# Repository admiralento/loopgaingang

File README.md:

# loopgaingang

EE372B project: a custom LDO test board (JAFWAK), and the tools to characterize it.

| Folder | What's in it |
|---|---|
| `LDO_Stable_JAFWAK/` | KiCad project for our board. Sub-sheets: `ldo_harness`, `buffer` (BUF634 for line transient / PSRR), `load_cell` (on-board switched load), `rc_filter`, `temp_sense`. Gerbers in `Out/`, BOM in `bom/`, PDFs in `Schematic PDFs/` and `LayoutLayers/`. |
| `TPS7A7001_Evaluation_Board/` | KiCad project for the TPS7A7001 demo board (1.0 V out), used to bring up the bench before our board. |
| `Switched_R_Load_Bank/` | KiCad project for the separate 5-bit switched resistor load used with the demo board. |
| `AD_workspaces/` | WaveForms workspaces and the JavaScript settling-time script for manual measurements with the Analog Discovery. |
| `ldo_bench/` | Python bench automation: load / line regulation, load / line transient, PSRR, quiescent current and enable tests, driven from the command line. **Start with [`ldo_bench/README.md`](ldo_bench/README.md).** |

The automated tests and the WaveForms workspaces use the same settling analysis (`ldo_bench` ports `AD_workspaces/load_tran_script.js`), so they give the same numbers.

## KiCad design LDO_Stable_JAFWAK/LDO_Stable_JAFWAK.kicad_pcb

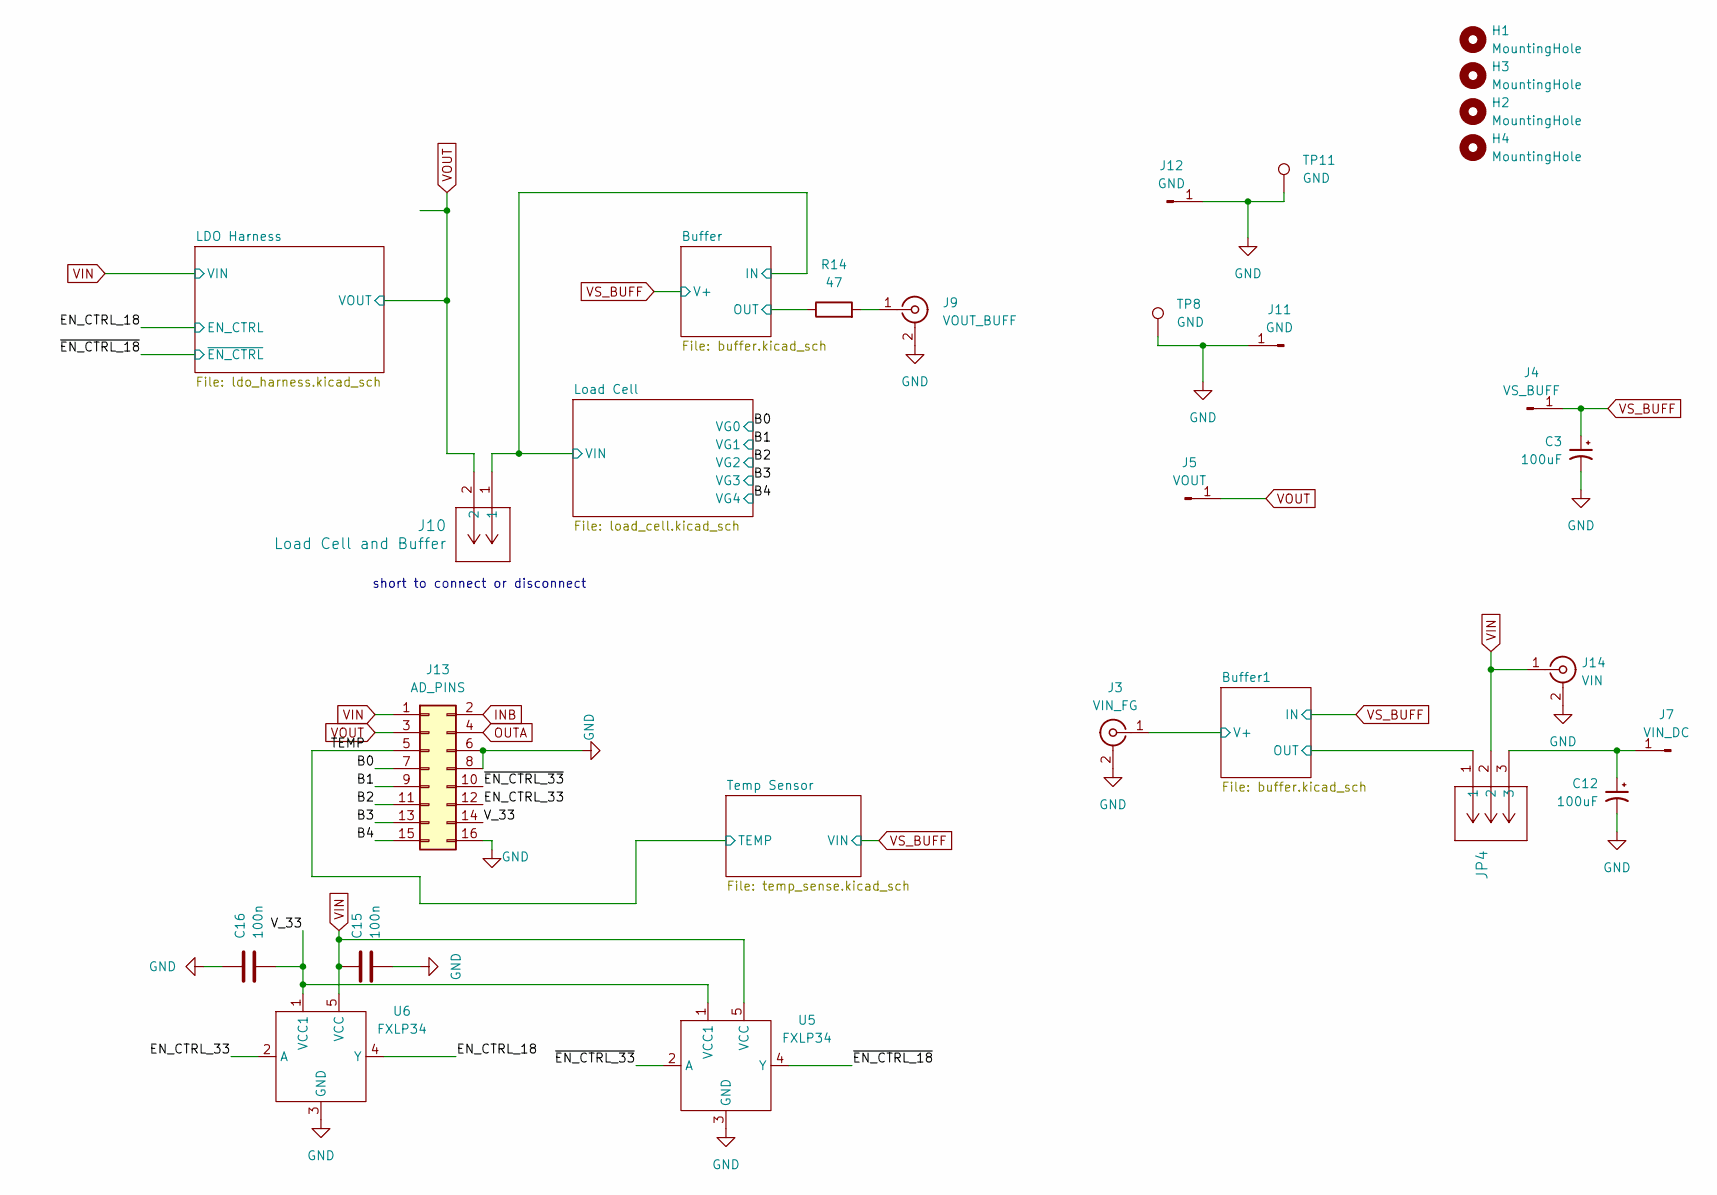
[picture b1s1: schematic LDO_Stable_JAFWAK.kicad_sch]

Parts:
C3, C12: 100uF; CAPPRD350W60D800H1150; Manufacturer Part Number EEU-FC1V101
C15, C16: 100n; C_0805_2012Metric_Pad1.18x1.45mm_HandSolder; Manufacturer Part Number C0805C102K5RACTU
H1, H2, H3, H4: MountingHole; MountingHole_2.5mm
J3: VIN_FG; SAMTEC_SMA-J-P-H-ST-TH1
J4: VS_BUFF; CALTEST_CT3151-2; Manufacturer Part Number CT3151SP-2
J5: VOUT; CALTEST_CT3151-2; Manufacturer Part Number CT3151SP-6
J7: VIN_DC; CALTEST_CT3151-2; Manufacturer Part Number CT3151SP-2
J9: VOUT_BUFF; SAMTEC_SMA-J-P-H-ST-TH1
J10: Load Cell and Buffer; PinHeader_1x02_P2.54mm_Vertical; Manufacturer Part Number PEC02SAAN
J11, J12: GND; CALTEST_CT3151-2; Manufacturer Part Number CT3151SP-0
J13: AD_PINS; PinHeader_2x08_P2.54mm_Vertical
J14: VIN; SAMTEC_SMA-J-P-H-ST-TH1
JP4: PEC03SAAN; PinHeader_1x03_P2.54mm_Vertical; Manufacturer Part Number PEC03SAAN
R14: 47; R_0805_2012Metric_Pad1.20x1.40mm_HandSolder; Manufacturer Part Number CRCW08050000Z0EAHP
TP8, TP11: GND; KEYSTONE_5016; Manufacturer Part Number 5016
U5, U6: FXLP34; SOT-353_SC-70-5

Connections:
/B0: J13.7; also elsewhere on the board
/B1: J13.9; also elsewhere on the board
/B2: J13.11; also elsewhere on the board
/B3: J13.13; also elsewhere on the board
/B4: J13.15; also elsewhere on the board
/Buffer1/OUT: JP4.1; also elsewhere on the board
/Buffer1/V+: J3.1 (In); also elsewhere on the board
/Buffer/IN: J10.1; also elsewhere on the board
/Buffer/OUT: R14.1; also elsewhere on the board
/EN_CTRL_18: U6.4 (Y); also elsewhere on the board
/EN_CTRL_33: J13.12, U6.2 (A)
/TEMP: J13.5; also elsewhere on the board
/V_33: C16.2, J13.14, U5.1 (VCC1), U6.1 (VCC1)
/~EN_CTRL_18: U5.4 (Y); also elsewhere on the board
/~EN_CTRL_33: J13.10, U5.2 (A)
GND: C3.N, C12.N, C15.2, C16.1, J3.2 (Ext), J3.3 (Ext), J3.4 (Ext), J3.5 (Ext), J9.2 (Ext), J9.3 (Ext), J9.4 (Ext), J9.5 (Ext), J11.1 (Pin_1_1), J12.1 (Pin_1_1), J13.6, J13.8, J13.16, J14.2 (Ext), J14.3 (Ext), J14.4 (Ext), J14.5 (Ext), TP8.1 (1_1), TP11.1 (1_1), U5.3 (GND), U6.3 (GND); also elsewhere on the board
INB: J13.2; also elsewhere on the board
unnamed: C12.P, J7.1 (Pin_1_1), JP4.3
unnamed: J9.1 (In), R14.2
OUTA: J13.4; also elsewhere on the board
VIN: C15.1, J13.1, J14.1 (In_1), JP4.2, U5.5 (VCC), U6.5 (VCC); also elsewhere on the board
VOUT: J5.1 (Pin_1_1), J10.2, J13.3; also elsewhere on the board
VS_BUFF: C3.P, J4.1 (Pin_1_1); also elsewhere on the board

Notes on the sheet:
short to connect or disconnect

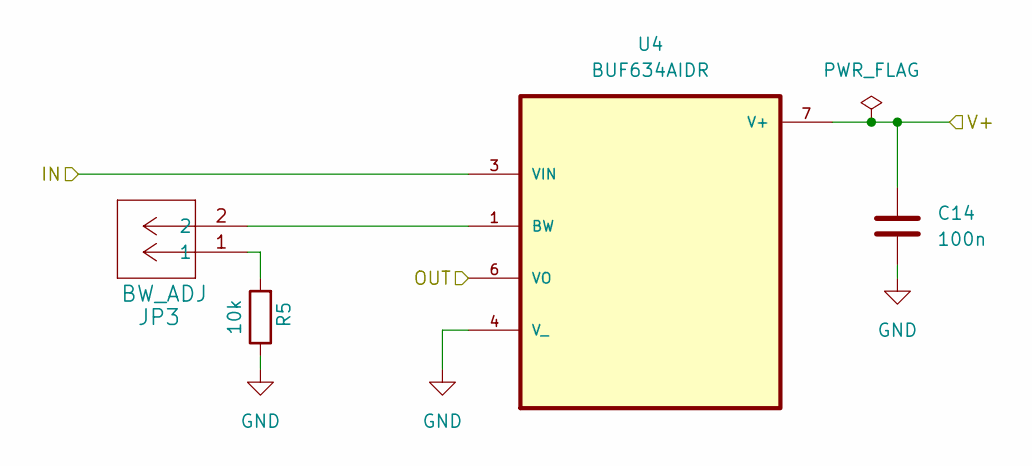
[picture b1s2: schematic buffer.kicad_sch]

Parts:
C14: 100n; C_0805_2012Metric_Pad1.18x1.45mm_HandSolder; Manufacturer Part Number C0805C106K8RACTU
JP3: BW_ADJ; PinHeader_1x02_P2.54mm_Vertical; Manufacturer Part Number PEC02SAAN
R5: 10k; R_0805_2012Metric_Pad1.20x1.40mm_HandSolder; Manufacturer Part Number RC0805FR-0710KL
U4: BUF634AIDR; SOIC127P599X175-8N; Manufacturer Part Number BUF634AIDR

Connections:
/Buffer/IN: U4.3 (VIN); also elsewhere on the board
/Buffer/OUT: U4.6 (VO); also elsewhere on the board
GND: C14.1, R5.1, U4.4 (V_); also elsewhere on the board
unnamed: JP3.1, R5.2
unnamed: JP3.2, U4.1 (BW)
VS_BUFF: C14.2, U4.7 (V+); also elsewhere on the board

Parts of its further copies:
C8: 100n; C_0805_2012Metric_Pad1.18x1.45mm_HandSolder; Manufacturer Part Number C0805C106K8RACTU
JP1: BW_ADJ; PinHeader_1x02_P2.54mm_Vertical; Manufacturer Part Number PEC02SAAN
R3: 10k; R_0805_2012Metric_Pad1.20x1.40mm_HandSolder; Manufacturer Part Number RC0805FR-0710KL
U2: BUF634AIDR; SOIC127P599X175-8N; Manufacturer Part Number BUF634AIDR

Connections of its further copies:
/Buffer1/OUT: U2.6 (VO); also elsewhere on the board
/Buffer1/V+: C8.2, U2.7 (V+); also elsewhere on the board
GND: C8.1, R3.1, U2.4 (V_); also elsewhere on the board
unnamed: JP1.1, R3.2
unnamed: JP1.2, U2.1 (BW)
VS_BUFF: U2.3 (VIN); also elsewhere on the board

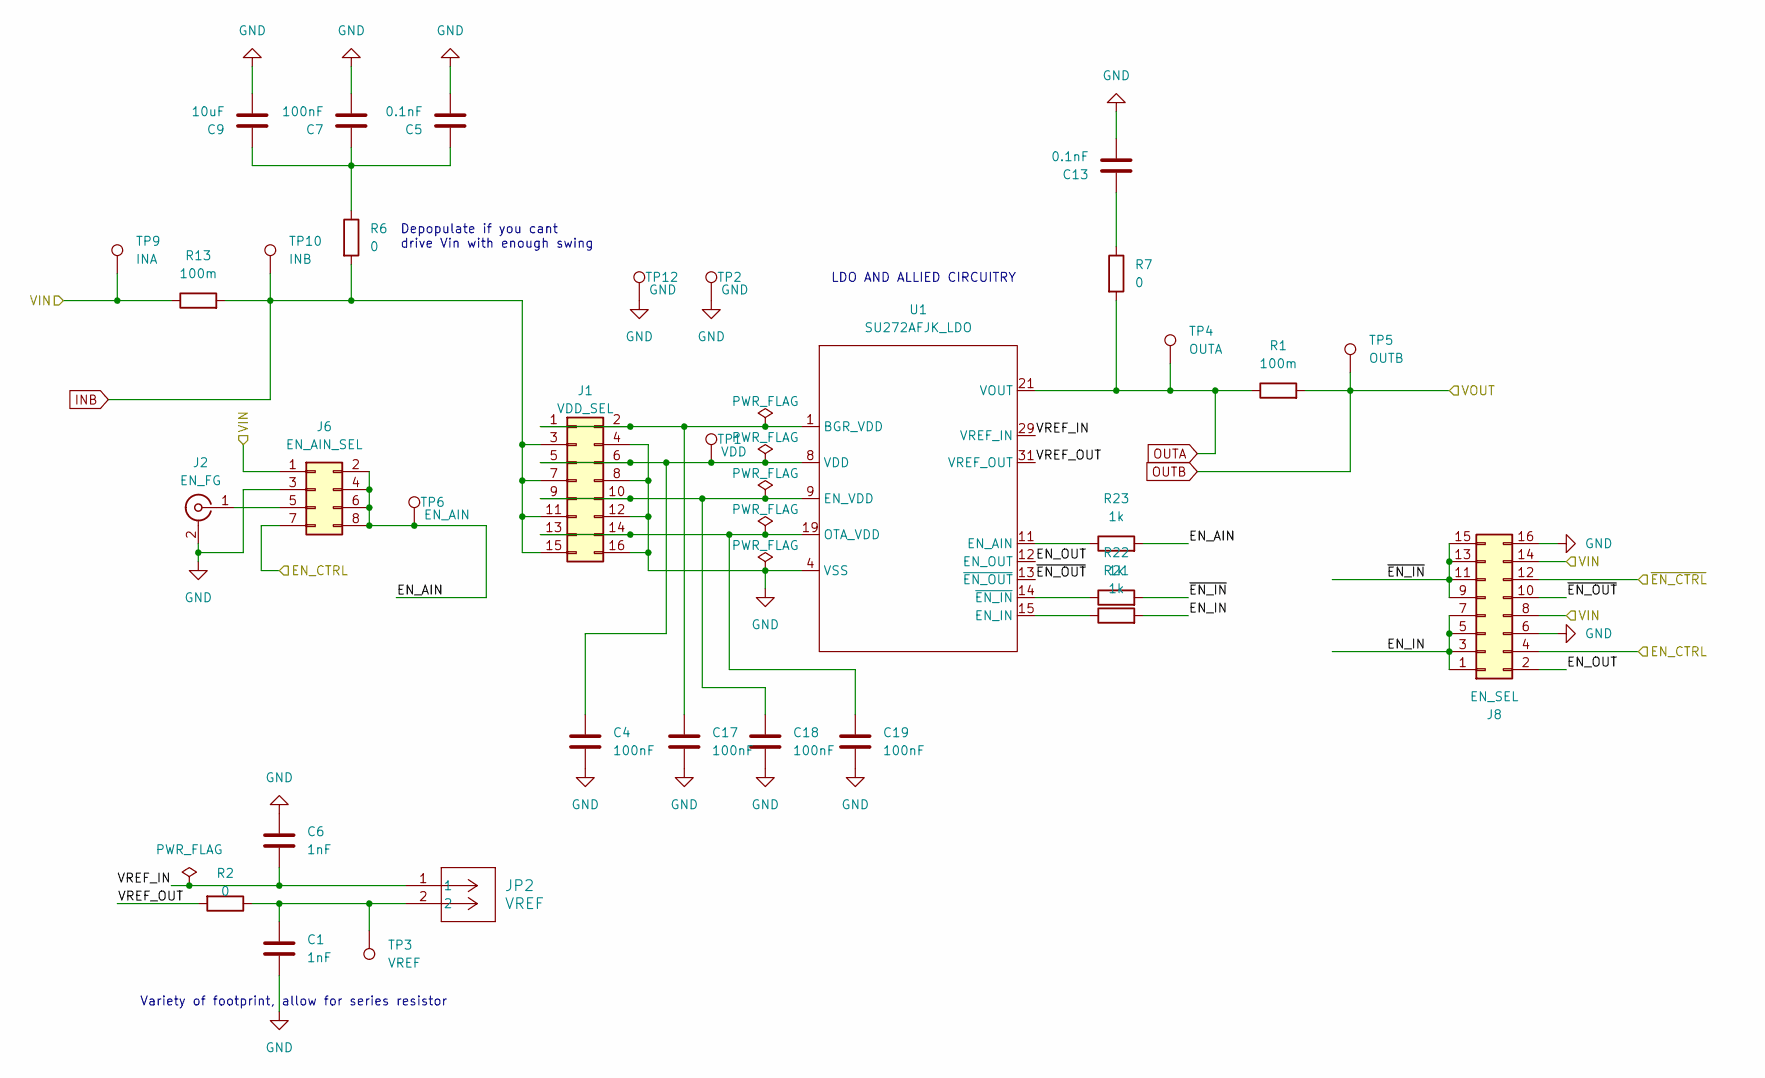
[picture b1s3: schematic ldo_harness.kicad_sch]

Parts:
C1, C6: 1nF; C_0805_2012Metric_Pad1.18x1.45mm_HandSolder
C4, C17, C18, C19: 100nF; C_0603_1608Metric; Manufacturer Part Number C0805C104K8RACTU
C5, C13: 0.1nF; C_0805_2012Metric_Pad1.18x1.45mm_HandSolder; Manufacturer Part Number C0805C101K8RACTU
C7: 100nF; C_0805_2012Metric_Pad1.18x1.45mm_HandSolder; Manufacturer Part Number C0805C104K8RACTU
C9: 10uF; C_0805_2012Metric_Pad1.18x1.45mm_HandSolder; Manufacturer Part Number C0805C106K8RACTU
J1: VDD_SEL; PinHeader_2x08_P2.54mm_Vertical
J2: EN_FG; SAMTEC_SMA-J-P-H-ST-TH1
J6: EN_AIN_SEL; PinHeader_2x04_P2.54mm_Vertical
J8: EN_SEL; PinHeader_2x08_P2.54mm_Vertical
JP2: VREF; PinHeader_1x02_P2.54mm_Vertical; Manufacturer Part Number PEC02SAAN
R1, R13: 100m; R_2512_6332Metric_Pad1.40x3.35mm_HandSolder; Manufacturer Part Number PA2512FKE7W0R1E
R2, R6, R7: 0; R_0805_2012Metric_Pad1.20x1.40mm_HandSolder; Manufacturer Part Number CRCW08050000Z0EAHP
R21, R22, R23: 1k; R_0603_1608Metric
TP1: VDD; KEYSTONE_5016; Manufacturer Part Number 5016
TP2, TP12: GND; KEYSTONE_5016; Manufacturer Part Number 5016
TP3: VREF; KEYSTONE_5016; Manufacturer Part Number 5016
TP4: OUTA; KEYSTONE_5016; Manufacturer Part Number 5016
TP5: OUTB; KEYSTONE_5016; Manufacturer Part Number 5016
TP6: EN_AIN; KEYSTONE_5016; Manufacturer Part Number 5016
TP9: INA; KEYSTONE_5016; Manufacturer Part Number 5016
TP10: INB; KEYSTONE_5016; Manufacturer Part Number 5016
U1: SU272AFJK_LDO; QFN-32-1EP_7x7mm_P0.65mm_EP5.4x5.4mm_ThermalVias

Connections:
/EN_CTRL_18: J6.7, J8.4; also elsewhere on the board
/LDO Harness/EN_AIN: J6.2, J6.4, J6.6, J6.8, R23.2, TP6.1 (1_1)
/LDO Harness/EN_IN: J8.1, J8.3, J8.5, J8.7, R21.2
/LDO Harness/EN_OUT: J8.2, U1.12 (EN_OUT)
/LDO Harness/VREF_IN: C6.2, JP2.1, U1.29 (VREF_IN)
/LDO Harness/VREF_OUT: R2.2, U1.31 (VREF_OUT)
/LDO Harness/~EN_IN: J8.9, J8.11, J8.13, J8.15, R22.2
/LDO Harness/~EN_OUT: J8.10, U1.13 (~EN_OUT)
/~EN_CTRL_18: J8.12; also elsewhere on the board
BGR_VDD: C17.1, J1.1, J1.2, U1.1 (BGR_VDD), U1.2 (BGR_VDD)
EN_VDD: C18.1, J1.9, J1.10, U1.9 (EN_VDD), U1.10 (EN_VDD)
GND: C1.2, C4.2, C5.2, C6.1, C7.2, C9.2, C13.2, C17.2, C18.2, C19.2, J1.4, J1.8, J1.12, J1.16, J2.2 (Ext), J2.3 (Ext), J2.4 (Ext), J2.5 (Ext), J6.3, J8.6, J8.16, TP2.1 (1_1), TP12.1 (1_1), U1.4 (VSS), U1.5 (VSS), U1.6 (VSS), U1.7 (VSS), U1.17 (VSS), U1.18 (VSS), U1.23 (VSS), U1.28 (VSS), U1.30 (VSS); also elsewhere on the board
INB: J1.3, J1.7, J1.11, J1.15, R6.2, R13.2, TP10.1 (1_1); also elsewhere on the board
unnamed: C1.1, JP2.2, R2.1, TP3.1 (1_1)
unnamed: C5.1, C7.1, C9.1, R6.1
unnamed: C13.1, R7.1
unnamed: J2.1 (In), J6.5
unnamed: R23.1, U1.11 (EN_AIN)
unnamed: R21.1, U1.15 (EN_IN)
unnamed: R22.1, U1.14 (~EN_IN)
OTA_VDD: C19.1, J1.13, J1.14, U1.19 (OTA_VDD), U1.20 (OTA_VDD)
OUTA: R1.1, R7.2, TP4.1 (1_1), U1.21 (VOUT), U1.22 (VOUT); also elsewhere on the board
VDD: C4.1, J1.5, J1.6, TP1.1 (1_1), U1.3 (VDD), U1.8 (VDD), U1.16 (VDD), U1.24 (VDD), U1.25 (VDD), U1.26 (VDD), U1.27 (VDD), U1.32 (VDD)
VIN: J6.1, J8.8, J8.14, R13.1, TP9.1 (1_1); also elsewhere on the board
VOUT: R1.2, TP5.1 (1_1); also elsewhere on the board

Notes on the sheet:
Variety of footprint, allow for series resistor
LDO AND ALLIED CIRCUITRY
Depopulate if you cant drive Vin with enough swing

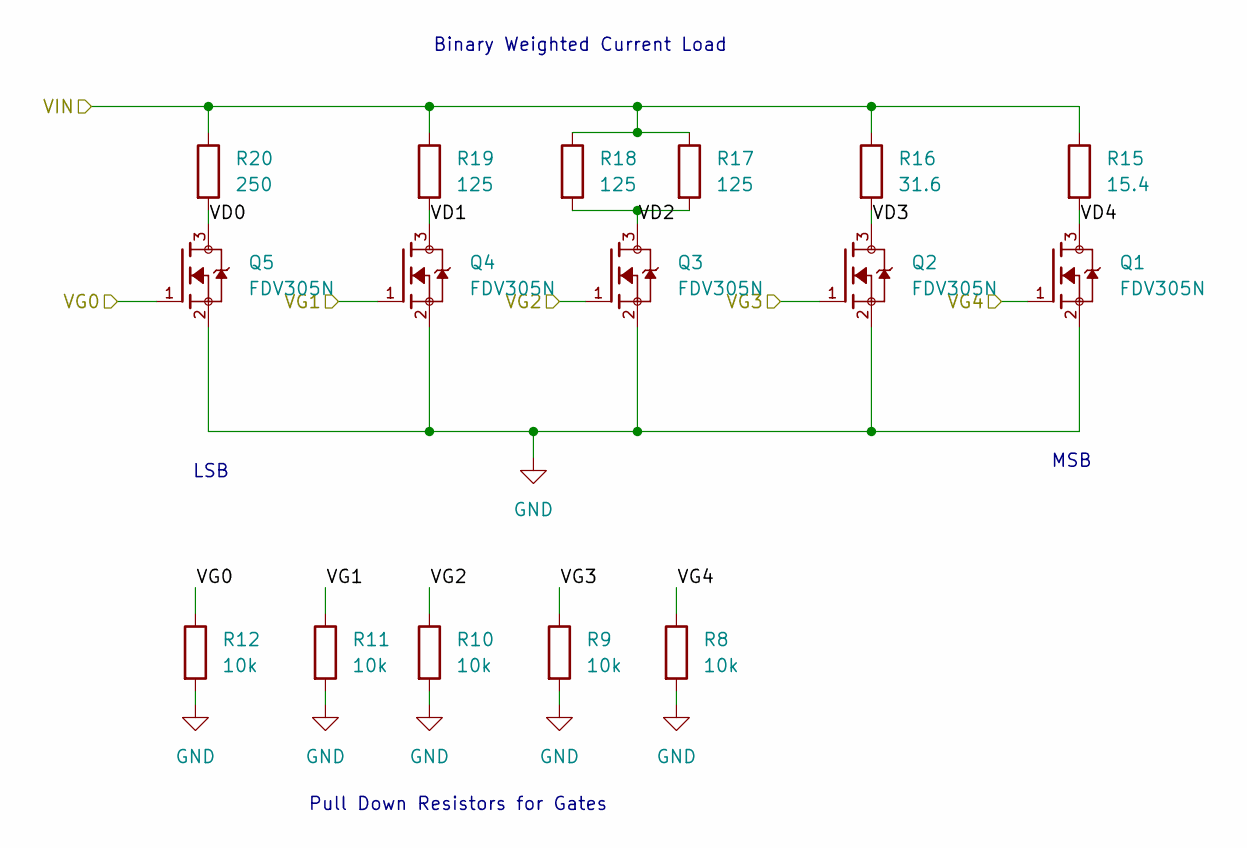
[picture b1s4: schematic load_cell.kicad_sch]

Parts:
Q1, Q2, Q3, Q4, Q5: FDV305N; TSOT-23; Manufacturer Part Number FDV305N
R8, R9, R10, R11, R12: 10k; R_0805_2012Metric_Pad1.20x1.40mm_HandSolder; Manufacturer Part Number RC0805FR-0710KL
R15: 15.4; R_0805_2012Metric_Pad1.20x1.40mm_HandSolder; Manufacturer Part Number RQ73C2A15R4BTDF
R16: 31.6; R_0805_2012Metric_Pad1.20x1.40mm_HandSolder; Manufacturer Part Number RQ73C2A31R6BTD
R17, R18, R19: 125; R_0805_2012Metric_Pad1.20x1.40mm_HandSolder; Manufacturer Part Number RQ73C2A124RBTD
R20: 250; R_0805_2012Metric_Pad1.20x1.40mm_HandSolder; Manufacturer Part Number RQ73C2A249RBTD

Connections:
/B0: Q5.1, R12.1; also elsewhere on the board
/B1: Q4.1, R11.1; also elsewhere on the board
/B2: Q3.1, R10.1; also elsewhere on the board
/B3: Q2.1, R9.1; also elsewhere on the board
/B4: Q1.1, R8.1; also elsewhere on the board
/Buffer/IN: R15.1, R16.1, R17.1, R18.1, R19.1, R20.1; also elsewhere on the board
/Load Cell/VD0: Q5.3, R20.2
/Load Cell/VD1: Q4.3, R19.2
/Load Cell/VD2: Q3.3, R17.2, R18.2
/Load Cell/VD3: Q2.3, R16.2
/Load Cell/VD4: Q1.3, R15.2
GND: Q1.2, Q2.2, Q3.2, Q4.2, Q5.2, R8.2, R9.2, R10.2, R11.2, R12.2; also elsewhere on the board

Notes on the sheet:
LSB
Binary Weighted Current Load
Pull Down Resistors for Gates
MSB

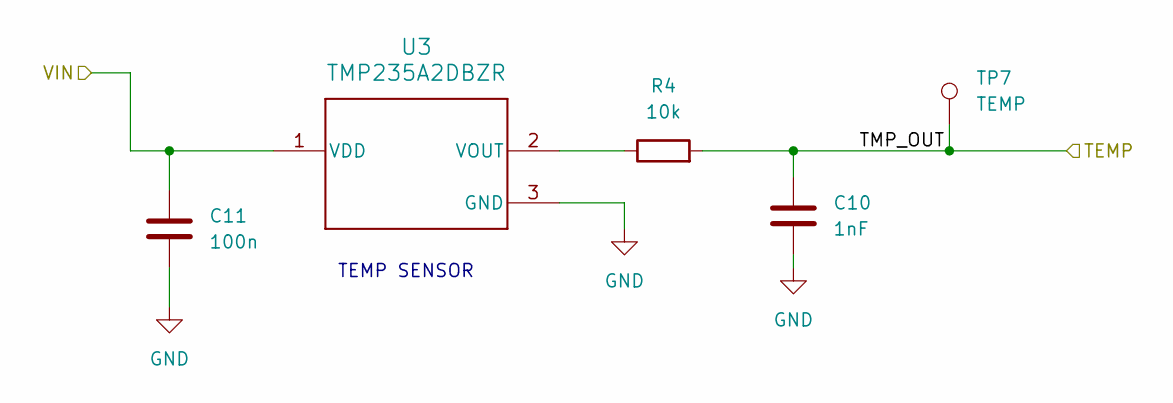
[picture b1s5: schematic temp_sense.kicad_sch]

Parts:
C10: 1nF; C_0805_2012Metric_Pad1.18x1.45mm_HandSolder; Manufacturer Part Number C0805C102K5RACTU
C11: 100n; C_0805_2012Metric_Pad1.18x1.45mm_HandSolder; Manufacturer Part Number C0805C102K5RACTU
R4: 10k; R_0805_2012Metric_Pad1.20x1.40mm_HandSolder; Manufacturer Part Number RC0805FR-0710KL
TP7: TEMP; KEYSTONE_5016; Manufacturer Part Number 5016
U3: TMP235A2DBZR; DBZ0003A-IPC_A; Manufacturer Part Number TMP235A2DBZR

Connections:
/TEMP: C10.1, R4.2, TP7.1 (1_1); also elsewhere on the board
GND: C10.2, C11.2, U3.3 (GND); also elsewhere on the board
unnamed: R4.1, U3.2 (VOUT)
VS_BUFF: C11.1, U3.1 (VDD); also elsewhere on the board

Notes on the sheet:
TEMP SENSOR

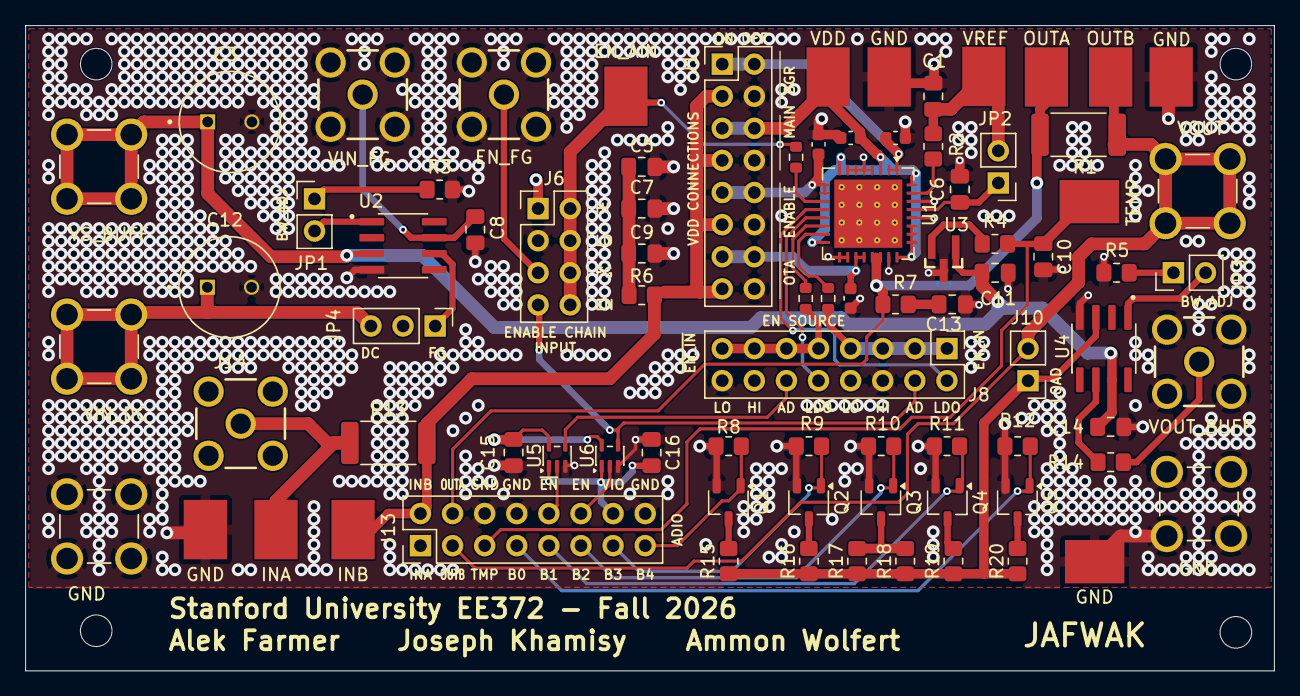
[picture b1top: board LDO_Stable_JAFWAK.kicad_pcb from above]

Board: 4 copper layers, 98.8 x 51.1 mm, 86 parts (0 on the bottom side), 51 nets.

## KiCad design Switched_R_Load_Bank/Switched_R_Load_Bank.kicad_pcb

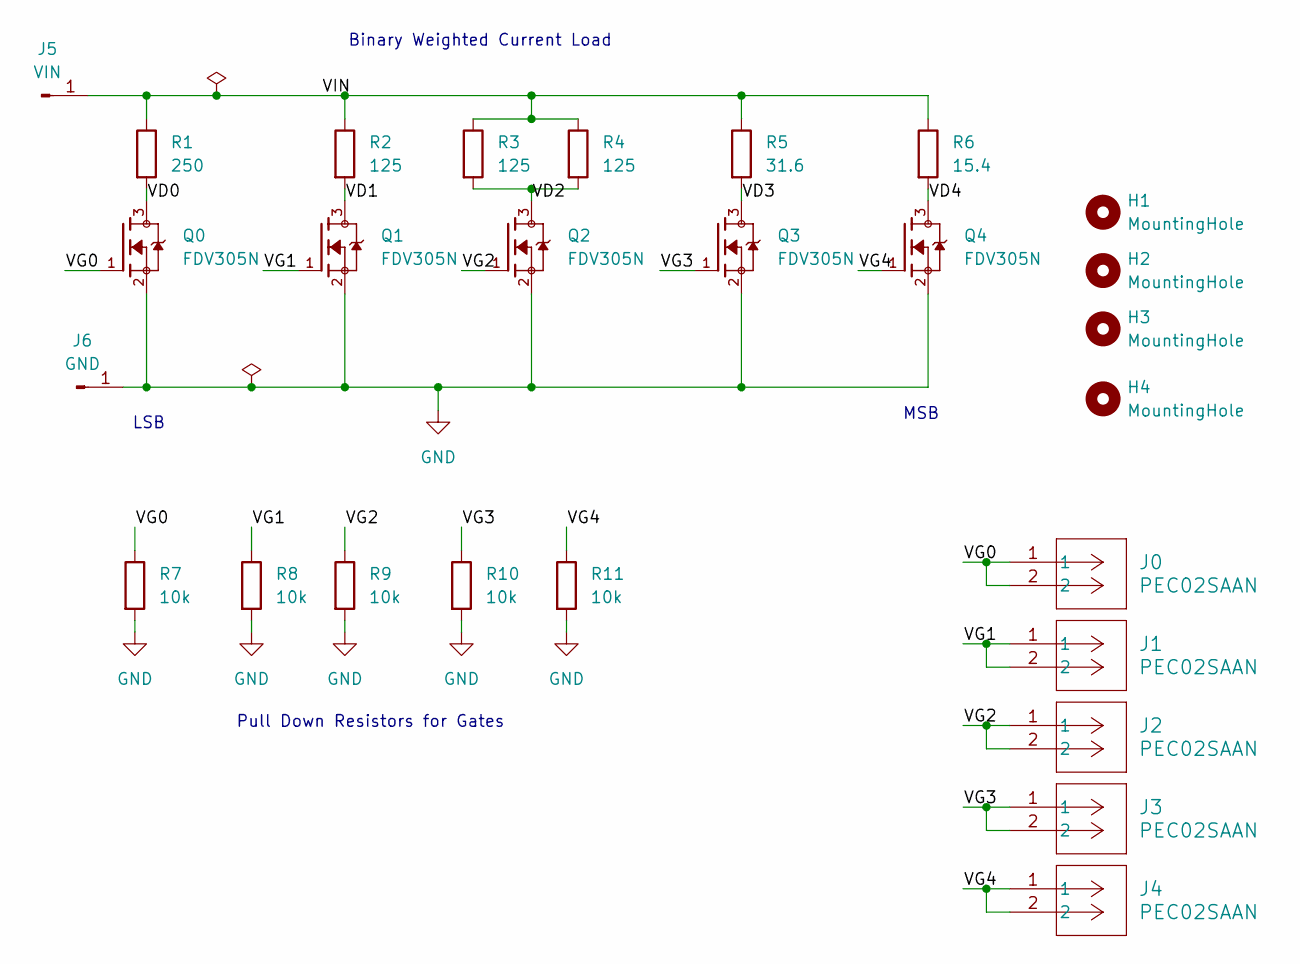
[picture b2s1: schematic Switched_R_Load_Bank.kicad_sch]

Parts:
H1, H2, H3, H4: MountingHole; MountingHole_2.5mm
J0, J1, J2, J3, J4: PEC02SAAN; CONN_PxC02S_SUL; Manufacturer Part Number PEC02SAAN
J5: VIN; CALTEST_CT3151-2; Manufacturer Part Number CT3151SP-2
J6: GND; CALTEST_CT3151-2; Manufacturer Part Number CT3151SP-0
Q0, Q1, Q2, Q3, Q4: FDV305N; SOT95P240X111-3N; Manufacturer Part Number FDV305N
R1: 250; R_0805_2012Metric_Pad1.20x1.40mm_HandSolder; Manufacturer Part Number RQ73C2A249RBTD
R2, R3, R4: 125; R_0805_2012Metric_Pad1.20x1.40mm_HandSolder; Manufacturer Part Number RQ73C2A124RBTD
R5: 31.6; R_0805_2012Metric_Pad1.20x1.40mm_HandSolder; Manufacturer Part Number RQ73C2A31R6BTD
R6: 15.4; R_0805_2012Metric_Pad1.20x1.40mm_HandSolder; Manufacturer Part Number RQ73C2A15R4BTDF
R7, R8, R9, R10, R11: 10k; R_0805_2012Metric_Pad1.20x1.40mm_HandSolder; Manufacturer Part Number RC0805FR-0710KL

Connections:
/VD0: Q0.3, R1.2
/VD1: Q1.3, R2.2
/VD2: Q2.3, R3.2, R4.2
/VD3: Q3.3, R5.2
/VD4: Q4.3, R6.2
/VG0: J0.1, J0.2, Q0.1, R7.1
/VG1: J1.1, J1.2, Q1.1, R8.1
/VG2: J2.1, J2.2, Q2.1, R9.1
/VG3: J3.1, J3.2, Q3.1, R10.1
/VG4: J4.1, J4.2, Q4.1, R11.1
/VIN: J5.1, R1.1, R2.1, R3.1, R4.1, R5.1, R6.1
GND: J6.1, Q0.2, Q1.2, Q2.2, Q3.2, Q4.2, R7.2, R8.2, R9.2, R10.2, R11.2

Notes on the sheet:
LSB
Binary Weighted Current Load
MSB
Pull Down Resistors for Gates

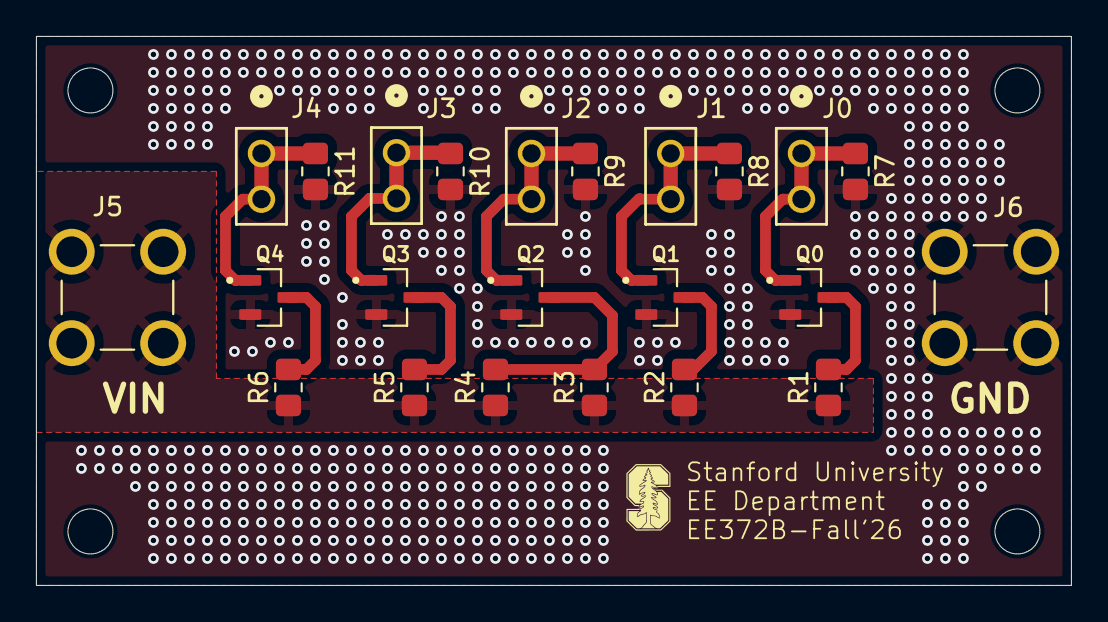
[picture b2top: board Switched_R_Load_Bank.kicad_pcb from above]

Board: 4 copper layers, 57.5 x 30.5 mm, 27 parts (0 on the bottom side), 12 nets.

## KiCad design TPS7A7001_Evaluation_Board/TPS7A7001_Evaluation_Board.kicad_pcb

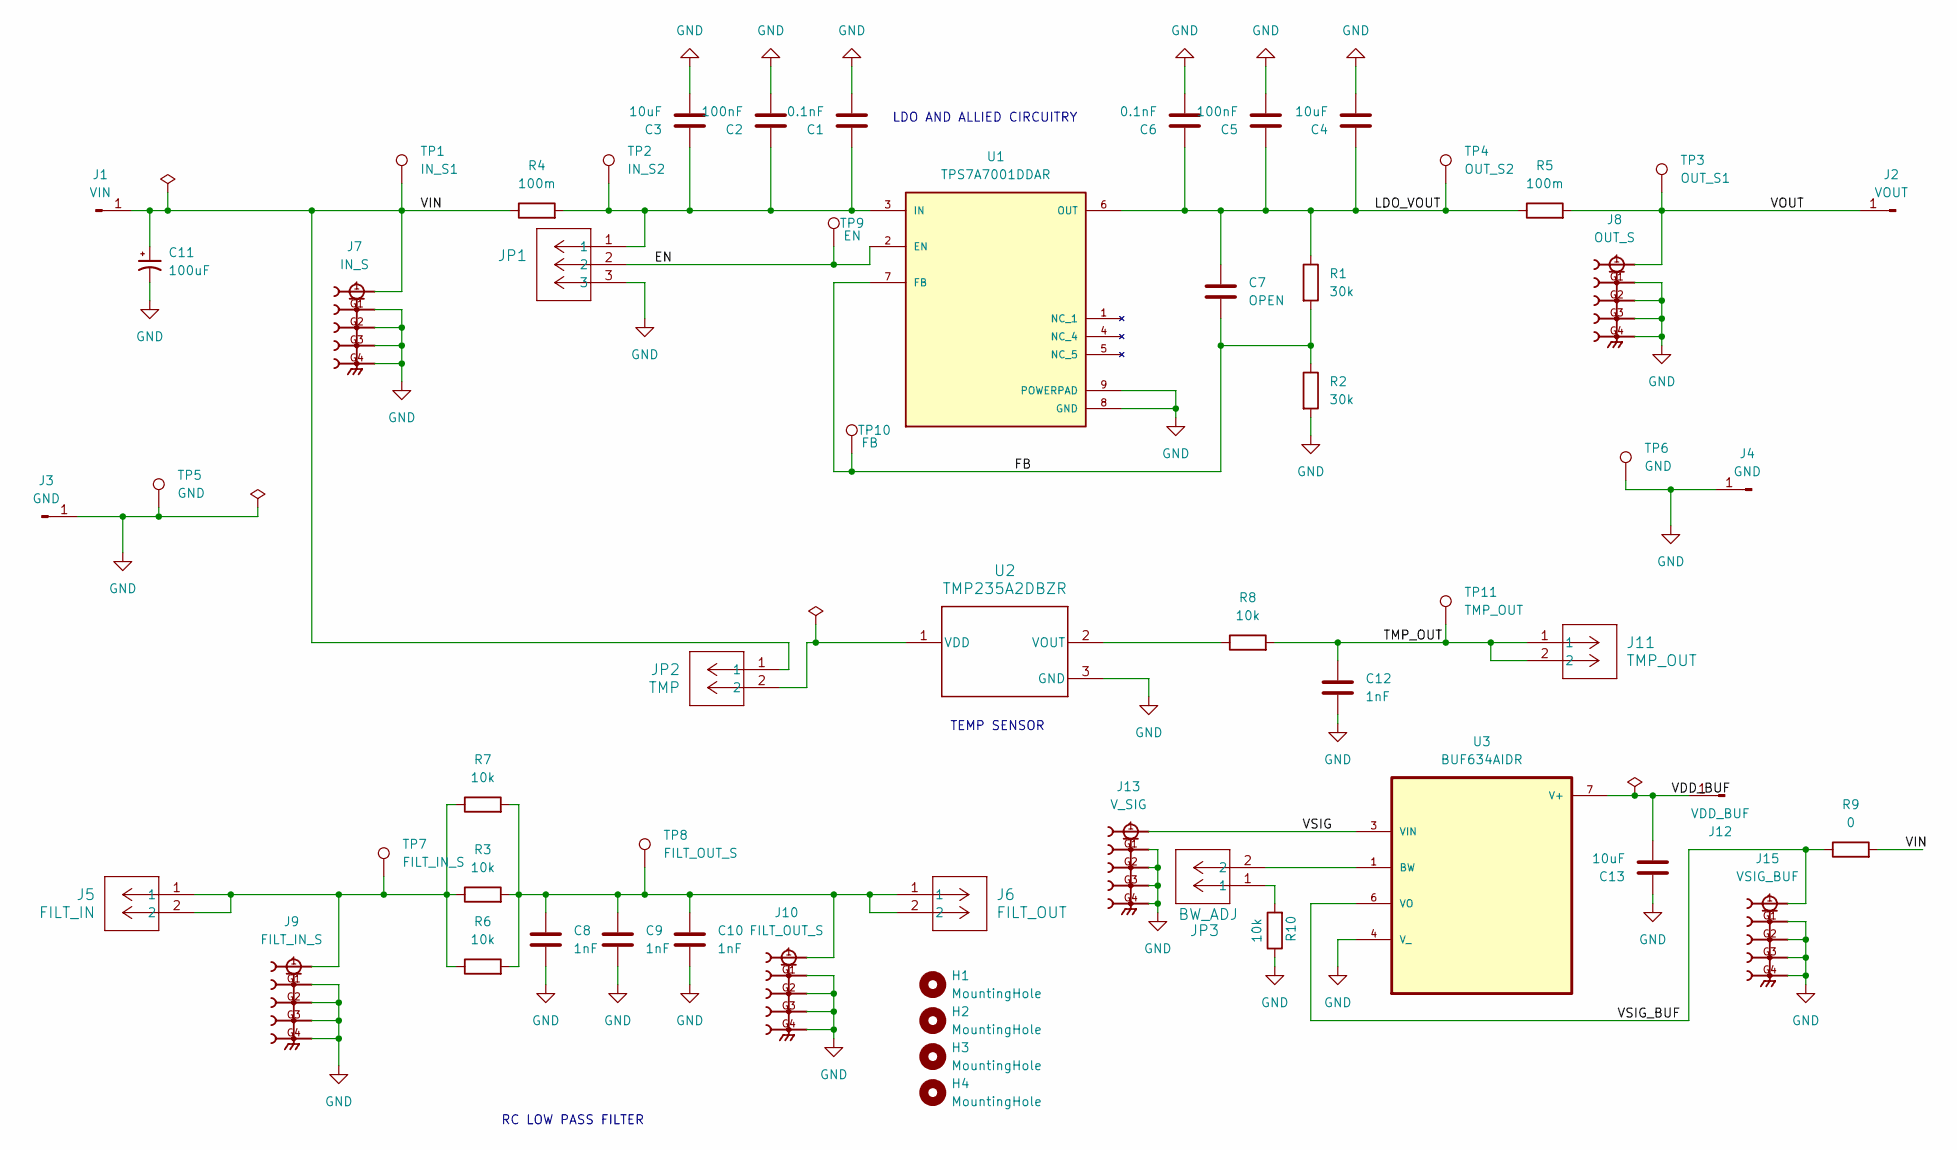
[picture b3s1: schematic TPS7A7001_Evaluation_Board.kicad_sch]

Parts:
C1, C6: 0.1nF; C_0805_2012Metric_Pad1.18x1.45mm_HandSolder; Manufacturer Part Number C0805C101K8RACTU
C2, C5: 100nF; C_0805_2012Metric_Pad1.18x1.45mm_HandSolder; Manufacturer Part Number C0805C104K8RACTU
C3, C4, C13: 10uF; C_0805_2012Metric_Pad1.18x1.45mm_HandSolder; Manufacturer Part Number C0805C106K8RACTU
C7: OPEN; C_0805_2012Metric_Pad1.18x1.45mm_HandSolder
C8, C9, C10, C12: 1nF; C_0805_2012Metric_Pad1.18x1.45mm_HandSolder; Manufacturer Part Number C0805C102K5RACTU
C11: 100uF; CAPPRD350W60D800H1150; Manufacturer Part Number EEU-FC1V101
H1, H2, H3, H4: MountingHole; MountingHole_2.5mm
J1: VIN; CALTEST_CT3151-2; Manufacturer Part Number CT3151SP-2
J2: VOUT; CALTEST_CT3151-2; Manufacturer Part Number CT3151SP-6
J3, J4: GND; CALTEST_CT3151-2; Manufacturer Part Number CT3151SP-0
J5: FILT_IN; CONN_PxC02S_SUL; Manufacturer Part Number PEC02SAAN
J6: FILT_OUT; CONN_PxC02S_SUL; Manufacturer Part Number PEC02SAAN
J7: IN_S; SAMTEC_SMA-J-P-H-ST-TH1; Manufacturer Part Number SMA-J-P-H-ST-TH1
J8: OUT_S; SAMTEC_SMA-J-P-H-ST-TH1; Manufacturer Part Number SMA-J-P-H-ST-TH1
J9: FILT_IN_S; SAMTEC_SMA-J-P-H-ST-TH1; Manufacturer Part Number SMA-J-P-H-ST-TH1
J10: FILT_OUT_S; SAMTEC_SMA-J-P-H-ST-TH1; Manufacturer Part Number SMA-J-P-H-ST-TH1
J11: TMP_OUT; CONN_PxC02S_SUL; Manufacturer Part Number PEC02SAAN
J12: VDD_BUF; CALTEST_CT3151-2; Manufacturer Part Number CT3151SP-2
J13: V_SIG; SAMTEC_SMA-J-P-H-ST-TH1; Manufacturer Part Number SMA-J-P-H-ST-TH1
J15: VSIG_BUF; SAMTEC_SMA-J-P-H-ST-TH1; Manufacturer Part Number SMA-J-P-H-ST-TH1
JP1: PEC03SAAN; CONN_PEC03SAAN_SUL; Manufacturer Part Number PEC03SAAN
JP2: TMP; CONN_PxC02S_SUL; Manufacturer Part Number PEC02SAAN
JP3: BW_ADJ; CONN_PxC02S_SUL; Manufacturer Part Number PEC02SAAN
R1, R2: 30k; R_0805_2012Metric_Pad1.20x1.40mm_HandSolder; Manufacturer Part Number RGT2012P-303-B-T5
R3, R6, R7, R8, R10: 10k; R_0805_2012Metric_Pad1.20x1.40mm_HandSolder; Manufacturer Part Number RC0805FR-0710KL
R4, R5: 100m; R_2512_6332Metric_Pad1.40x3.35mm_HandSolder; Manufacturer Part Number PA2512FKE7W0R1E
R9: 0; R_0805_2012Metric_Pad1.20x1.40mm_HandSolder; Manufacturer Part Number CRCW08050000Z0EAHP
TP1: IN_S1; KEYSTONE_5016; Manufacturer Part Number 5016
TP2: IN_S2; KEYSTONE_5016; Manufacturer Part Number 5016
TP3: OUT_S1; KEYSTONE_5016; Manufacturer Part Number 5016
TP4: OUT_S2; KEYSTONE_5016; Manufacturer Part Number 5016
TP5, TP6: GND; KEYSTONE_5016; Manufacturer Part Number 5016
TP7: FILT_IN_S; KEYSTONE_5016; Manufacturer Part Number 5016
TP8: FILT_OUT_S; KEYSTONE_5016; Manufacturer Part Number 5016
TP9: EN; KEYSTONE_5016; Manufacturer Part Number 5016
TP10: FB; KEYSTONE_5016; Manufacturer Part Number 5016
TP11: TMP_OUT; KEYSTONE_5016; Manufacturer Part Number 5016
U1: TPS7A7001DDAR; DDA0008E-IPC_A; Manufacturer Part Number TPS7A7001DDAR
U2: TMP235A2DBZR; DBZ0003A-IPC_A; Manufacturer Part Number TMP235A2DBZR
U3: BUF634AIDR; SOIC127P599X175-8N; Manufacturer Part Number BUF634AIDR

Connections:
/EN: JP1.2, TP9.1, U1.2 (EN)
/FB: C7.2, R1.2, R2.1, TP10.1, U1.7 (FB)
/LDO_VOUT: C4.1, C5.1, C6.1, C7.1, R1.1, R5.1, TP4.1, U1.6 (OUT)
/TMP_OUT: C12.1, J11.1, J11.2, R8.2, TP11.1
/VDD_BUF: C13.2, J12.1, U3.7 (V+)
/VIN: C11.P, J1.1, J7.1, JP2.1, R4.1, R9.2, TP1.1
/VOUT: J2.1, J8.1, R5.2, TP3.1
/VSIG: J13.1, U3.3 (VIN)
/VSIG_BUF: J15.1, R9.1, U3.6 (VO)
GND: C1.2, C2.2, C3.2, C4.2, C5.2, C6.2, C8.2, C9.2, C10.2, C11.N, C12.2, C13.1, J3.1, J4.1, J7.G1, J7.G2, J7.G3, J7.G4, J8.G1, J8.G2, J8.G3, J8.G4, J9.G1, J9.G2, J9.G3, J9.G4, J10.G1, J10.G2, J10.G3, J10.G4, J13.G1, J13.G2, J13.G3, J13.G4, J15.G1, J15.G2, J15.G3, J15.G4, JP1.3, R2.2, R10.1, TP5.1, TP6.1, U1.8 (GND), U1.9 (POWERPAD), U2.3 (GND), U3.4 (V_)
unnamed: C8.1, C9.1, C10.1, J6.1, J6.2, J10.1, R3.2, R6.2, R7.2, TP8.1
unnamed: J5.1, J5.2, J9.1, R3.1, R6.1, R7.1, TP7.1
unnamed: JP3.1, R10.2
unnamed: C1.1, C2.1, C3.1, JP1.1, R4.2, TP2.1, U1.3 (IN)
unnamed: JP2.2, U2.1 (VDD)
unnamed: R8.1, U2.2 (VOUT)
unnamed: JP3.2, U3.1 (BW)

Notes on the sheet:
TEMP SENSOR
RC LOW PASS FILTER
LDO AND ALLIED CIRCUITRY

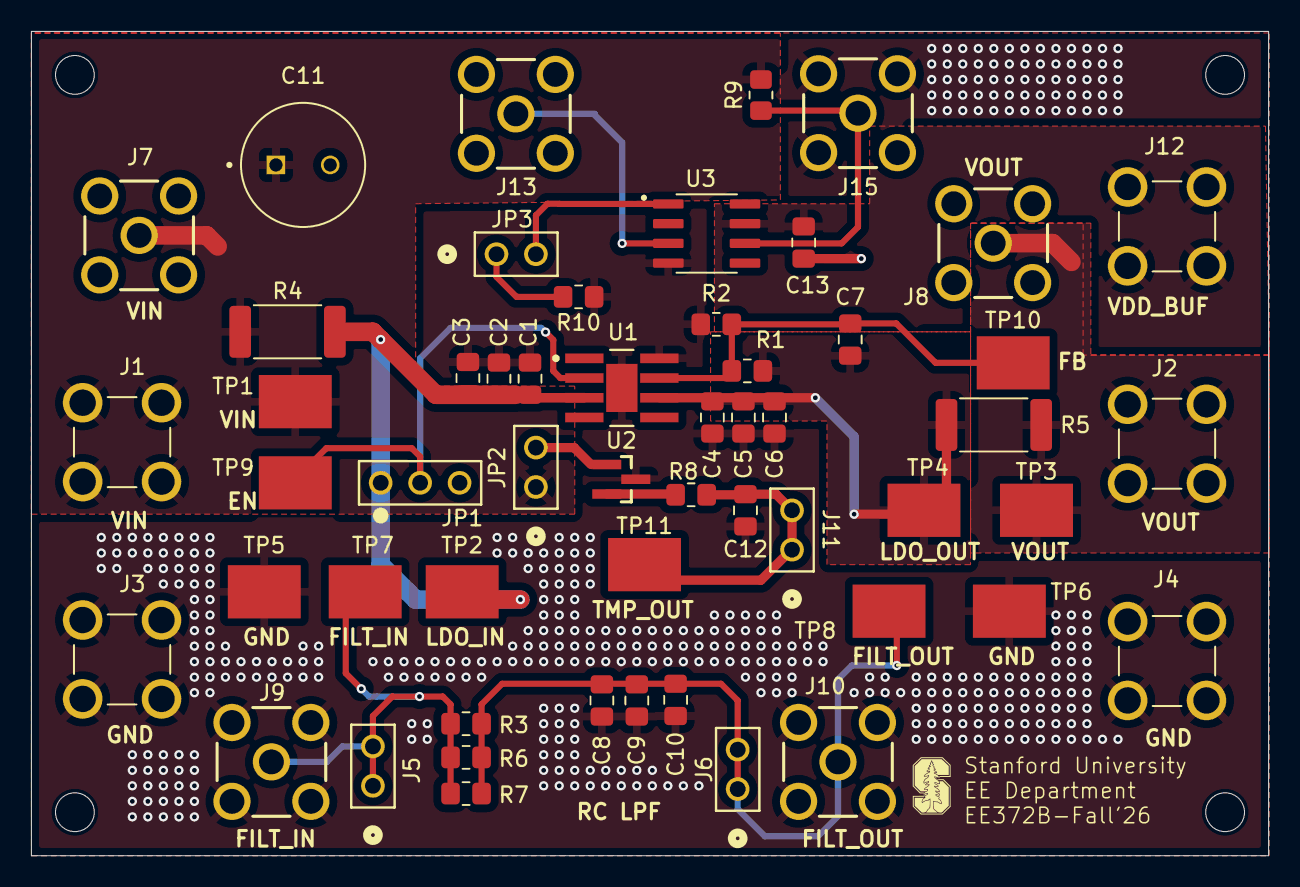
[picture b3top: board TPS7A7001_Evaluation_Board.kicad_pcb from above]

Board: 4 copper layers, 79.7 x 53.1 mm, 58 parts (0 on the bottom side), 17 nets.
